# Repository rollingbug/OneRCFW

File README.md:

# OneRCFW
An Arduino/AVR based flight controller for RC fixed wing.  

    - 5 input channels (Throttle, Ailerons, Elevator, Rudder, flight mode)  
    - 4 output channels (0.5 us resolution PWM/PPM signal generator).  
    - Airplane NED attitude tracking function (with 6 DOF sensor, 200 Hz attitude update rate).
    - Airplane auto level (roll and pitch) control function.  
    - Airplane heading lock control function.  
    - Airplane flight mode control function (manual mode, auto level mode and GPS mode).  
    - Airplane GPS return to home function (unstabled, still need to do more test!)
    - RC output mixer function (for normal airplane, delta wing and V tail).  
    - 6 DOF sensor calibration function.  
    - Radio control stick position calibration function.    
    - Airplane failsafe function.  
    - Airplane configuration save/reload/reset function.  
    - Airplane runtime status monitoring function.  

  <br/><br/><br/>

Details:
---------------------
Flight controller source code: [OneRCFW](https://github.com/rollingbug/OneRCFW/tree/master/OneRCFW)  
Flight controller schematic and PCB layout: [OneRCSchematic_v1](https://github.com/rollingbug/OneRCFW/tree/master/OneRCSchematic/OneRCSchematic_v1)  
Flight controller test video: [20171029 FC test in very windy (12.5m/s) day.](https://www.youtube.com/watch?v=OjTpQ1Ft-OE)  
GUI monitoring tool: [OneRCGUI](https://github.com/rollingbug/OneRCFW/tree/master/OneRCGUI)  
Design documents: [OneRCDesignDoc](https://github.com/rollingbug/OneRCFW/tree/master/OneRCDesignDoc)   

Build and Installation:
---------------------
1. Prepare Arduino 1.6.9 IDE.
2. Click the **OneRCAirplane.ino** to launch Arduino IDE. 
3. Change board type setting to "Arduino Nano" or "Pro Mini" and correct UART port setting.
4. Build and upload the firmware to Arduino or customized PCB.
5. Connect the Radio receiver to flight controller.
6. Check the channel output signal and the status of on board LEDs.<br/><br/><br/>

For Simulation mode:
---------------------
1. Download and instll FlightGear, and copy the protocol and configuration file to speicfic folder.
    - Copy [MAVLink.xml](https://github.com/rollingbug/OneRCFW/tree/master/OneRCFlightGearConf/MAVLink.xml) to FlightGear\data\Protocol\
    - Copy [.fgfsrc](https://github.com/rollingbug/OneRCFW/tree/master/OneRCFlightGearConf/.fgfsrc) to C:\Documents and Settings\{User name}\
2. Modify the #define IMU_SENSOR_MPU6050 in imu_ctrl.h, change to #define IMU_SENSOR_FG_SIM.
3. Rebuild and upload the firmware to Arduino.
4. Modify the COM port setting in both the [MP_fdm_nmea.py](https://github.com/rollingbug/OneRCFW/tree/master/OneRCGUI/MP_fdm_nmea.py) and [MP_fdm_sim.py](https://github.com/rollingbug/OneRCFW/tree/master/OneRCGUI/MP_fdm_sim.py), and lanuch these 2 files.
5. Lanuch fgfs.exe and enjoy the flight in simulator.

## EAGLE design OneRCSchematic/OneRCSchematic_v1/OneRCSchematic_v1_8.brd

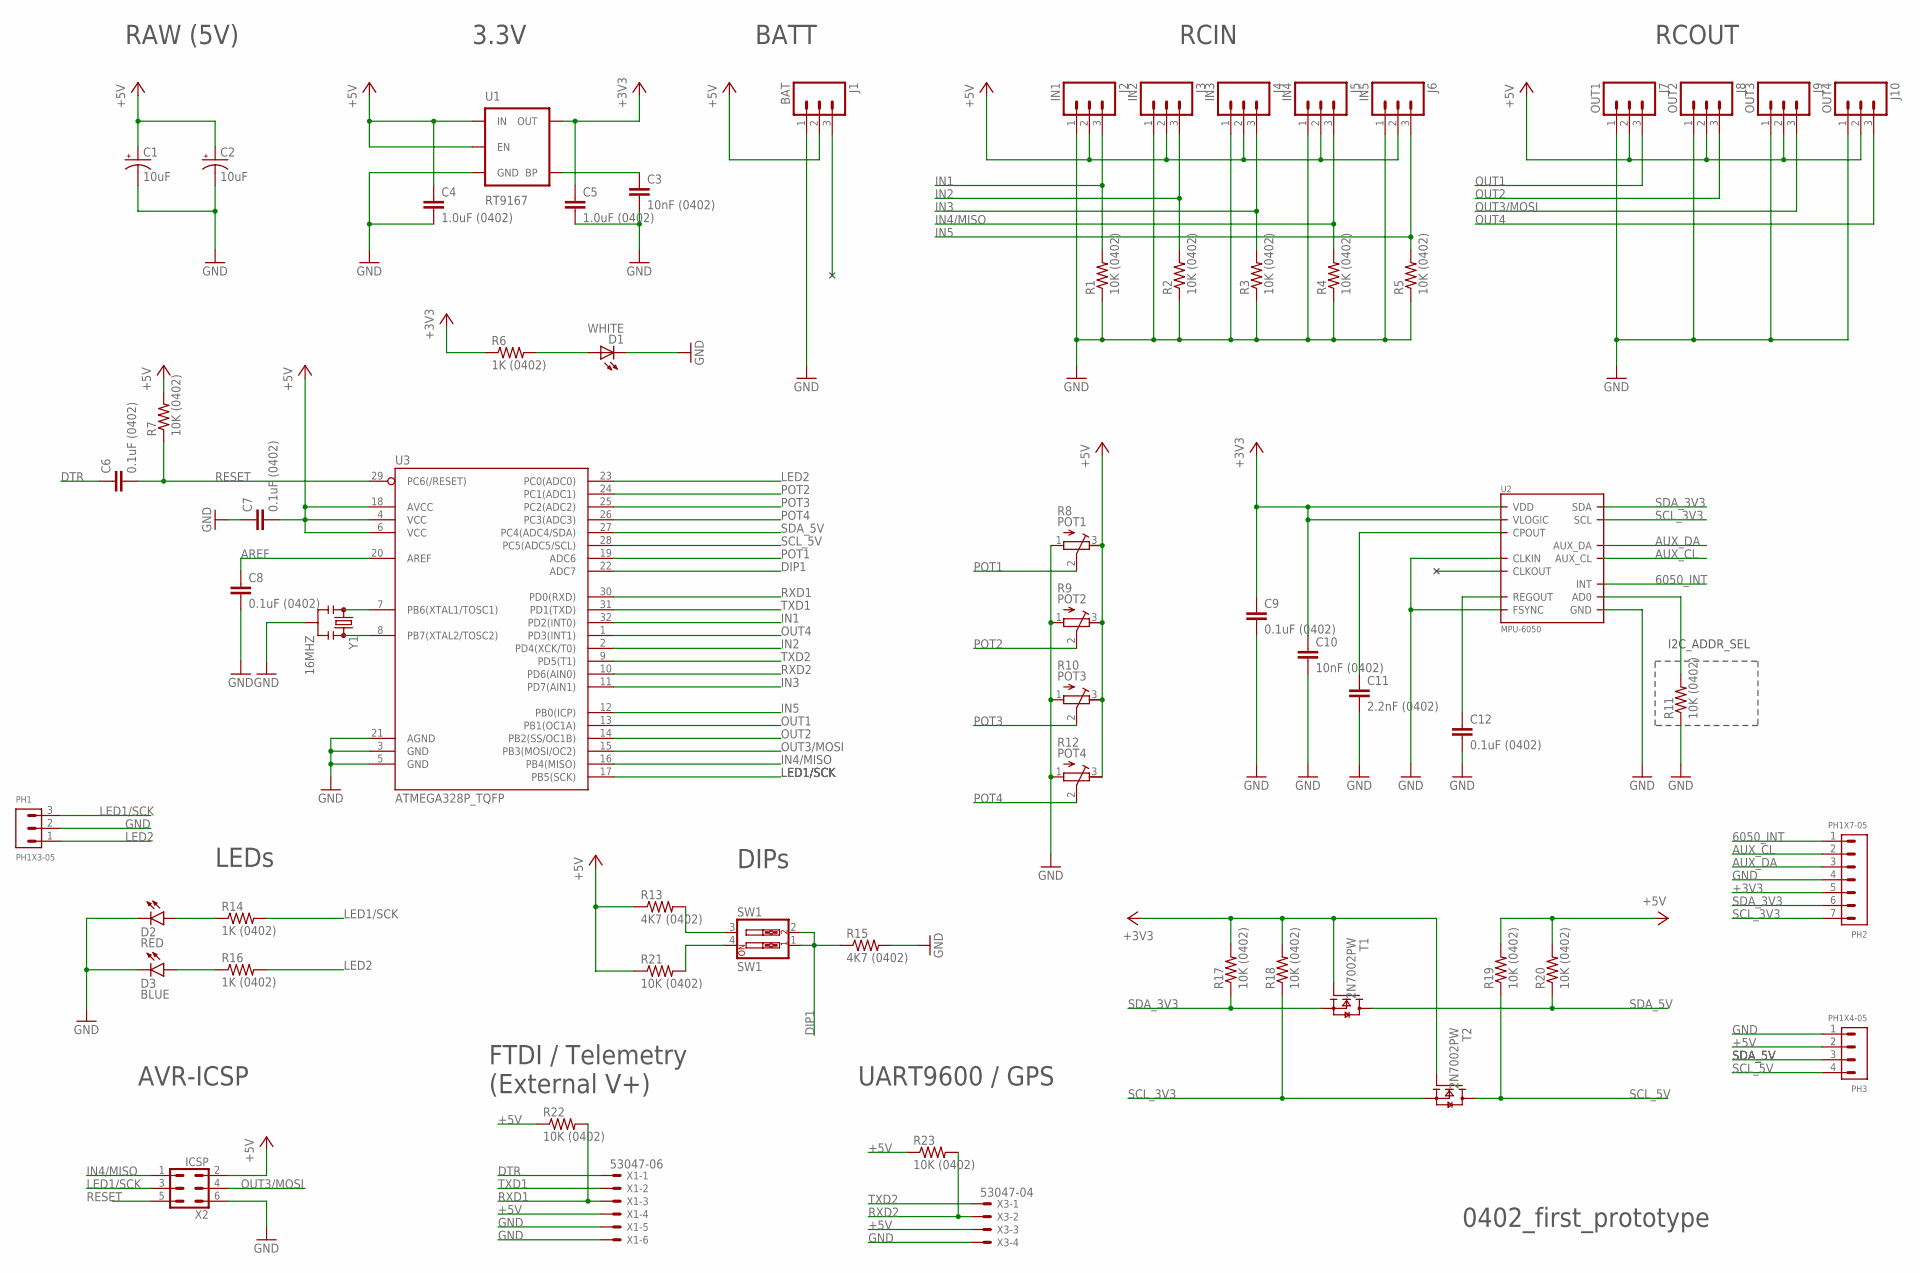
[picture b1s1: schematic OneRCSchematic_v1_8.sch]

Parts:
C1, C2: 10uF; EIA3216
C3, C10: 10nF (0402); 0402-CAP
C4, C5: 1.0uF (0402); 0402-CAP
C6, C7, C8, C9, C12: 0.1uF (0402); 0402-CAP
C11: 2.2nF (0402); 0402-CAP
D1: WHITE; 0402-LED
D2: RED; LED-0603
D3: BLUE; LED-0603
J1: BAT; 1X03
J2: IN1; 1X03
J3: IN2; 1X03
J4: IN3; 1X03
J5: IN4; 1X03
J6: IN5; 1X03
J7: OUT1; 1X03
J8: OUT2; 1X03
J9: OUT3; 1X03
J10: OUT4; 1X03
PH1: PH1X3-05; PH005-1-3
PH2: PH1X7-05; PH005-1-7
PH3: PH1X4-05; PH005-1-4
R1, R2, R3, R4, R5, R7, R11, R17, R18, R19, R20, R21, R22, R23: 10K (0402); 0402-RES
R6, R14, R16: 1K (0402); 0402-RES
R8: POT1; RTRIM3202
R9: POT2; RTRIM3202
R10: POT3; RTRIM3202
R12: POT4; RTRIM3202
R13, R15: 4K7 (0402); 0402-RES
SW1: SW1; DIPSWITCH-02-50MIL
T1, T2: 2N7002PW; SOT323
U1: RT9167; SOT23-5
U2: MPU-6050; QFN.24.4X4
U3: ATMEGA328P_TQFP; TQFP32-08
X1: 53047-06
X2: ICSP; PHB_1MM27_2X03_SNT
X3: 53047-04
Y1: 16MHZ; RESONATOR-SMD

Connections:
6050_INT: PH2.1, U2.12 (INT)
+3V3: C5.1, C9.1, C10.1, PH2.5, R6.1, R17.2, R18.2, T1.1 (G), T2.1 (G), U1.5 (OUT), U2.8 (VLOGIC), U2.13 (VDD)
+5V: C1.A (+), C2.A (+), C4.1, C7.2, J1.2, J2.2, J3.2, J4.2, J5.2, J6.2, J7.2, J8.2, J9.2, J10.2, PH3.2, R7.2, R8.3 (E), R9.3 (E), R10.3 (E), R12.3 (E), R13.1, R19.2, R20.2, R21.1, R22.1, R23.1, U1.1 (IN), U1.3 (EN), U3.4 (VCC), U3.6 (VCC), U3.18 (AVCC), X1.4, X2.2, X3.3
AREF: C8.1, U3.20 (AREF)
AUX_CL: PH2.2, U2.7 (AUX_CL)
AUX_DA: PH2.3, U2.6 (AUX_DA)
DIP1: R15.1, SW1.1, SW1.2, U3.22 (ADC7)
DTR: C6.1, X1.1
GND: C1.C (-), C2.C (-), C3.2, C4.2, C5.2, C7.1, C8.2, C9.2, C10.2, C11.2, C12.2, D1.C, D2.C, D3.C, J1.1, J2.1, J3.1, J4.1, J5.1, J6.1, J7.1, J8.1, J9.1, J10.1, PH1.2, PH2.4, PH3.1, R1.1, R2.1, R3.1, R4.1, R5.1, R8.1 (A), R9.1 (A), R10.1 (A), R11.1, R12.1 (A), R15.2, U1.2 (GND), U2.1 (CLKIN), U2.11 (FSYNC), U2.18 (GND), U3.3 (GND), U3.5 (GND), U3.21 (AGND), X1.5, X1.6, X2.6, X3.4, Y1.2
IN1: J2.3, R1.2, U3.32 (PD2(INT0))
IN2: J3.3, R2.2, U3.2 (PD4(XCK/T0))
IN3: J4.3, R3.2, U3.11 (PD7(AIN1))
IN4/MISO: J5.3, R4.2, U3.16 (PB4(MISO)), X2.1
IN5: J6.3, R5.2, U3.12 (PB0(ICP))
LED1/SCK: PH1.3, R14.2, U3.17 (PB5(SCK)), X2.3
LED2: PH1.1, R16.2, U3.23 (PC0(ADC0))
unnamed: D2.A, R14.1
unnamed: U3.7 (PB6(XTAL1/TOSC1)), Y1.1
unnamed: U3.8 (PB7(XTAL2/TOSC2)), Y1.3
unnamed: D3.A, R16.1
unnamed: D1.A, R6.2
unnamed: C3.1, U1.4 (BP)
unnamed: C11.1, U2.20 (CPOUT)
unnamed: C12.1, U2.10 (REGOUT)
unnamed: R13.2, SW1.3
unnamed: R21.2, SW1.4
unnamed: R11.2, U2.9 (AD0)
OUT1: J7.3, U3.13 (PB1(OC1A))
OUT2: J8.3, U3.14 (PB2(SS/OC1B))
OUT3/MOSI: J9.3, U3.15 (PB3(MOSI/OC2)), X2.4
OUT4: J10.3, U3.1 (PD3(INT1))
POT1: R8.2 (S), U3.19 (ADC6)
POT2: R9.2 (S), U3.24 (PC1(ADC1))
POT3: R10.2 (S), U3.25 (PC2(ADC2))
POT4: R12.2 (S), U3.26 (PC3(ADC3))
RESET: C6.2, R7.1, U3.29 (PC6(/RESET)), X2.5
RXD1: R22.2, U3.30 (PD0(RXD)), X1.3
RXD2: R23.2, U3.10 (PD6(AIN0)), X3.2
SCL_3V3: PH2.7, R18.1, T2.2 (S), U2.23 (SCL)
SCL_5V: PH3.4, R19.1, T2.3 (D), U3.28 (PC5(ADC5/SCL))
SDA_3V3: PH2.6, R17.1, T1.2 (S), U2.24 (SDA)
SDA_5V: PH3.3, R20.1, T1.3 (D), U3.27 (PC4(ADC4/SDA))
TXD1: U3.31 (PD1(TXD)), X1.2
TXD2: U3.9 (PD5(T1)), X3.1

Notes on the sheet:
LEDs
RCIN
RCOUT
3.3V
RAW (5V)
AVR-ICSP
FTDI / Telemetry (External V+)
UART9600 / GPS
DIPs
0402_first_prototype
I2C_ADDR_SEL
BATT

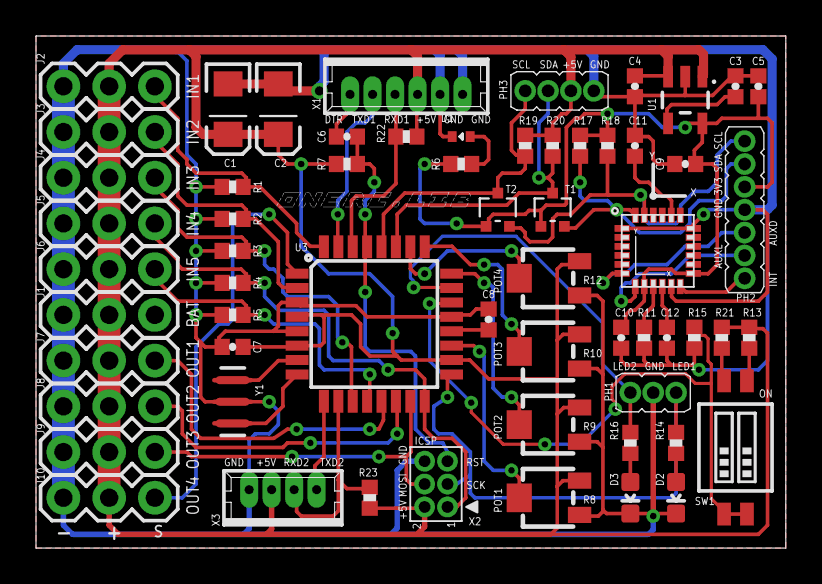
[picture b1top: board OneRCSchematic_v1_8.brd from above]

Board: 2 copper layers, 41.7 x 28.4 mm, 62 parts (0 on the bottom side), 44 nets.

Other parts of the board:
U$2: ONE_RX_LOG_TINY_TOP

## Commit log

2017-12-17 [OneRCFW]
    1. Import v0.1.0.
    - Auto level function.
    - Maintaining heading angle based on gyroscope.
    - FC configuration save/clean/load functions.
    - Return to home according to GPS navigation information (unstable, need to do more test).
    - RCIN calibration functions:
2018-01-21 [OneRCFW]
    1. Add design documents and update README.md.
2018-01-21 [OneRCFW]
    1. Picture link test.
2018-01-21 [OneRCFW]
    1. Rearranged README.md.
2018-01-21 [OneRCFW]
    1. Sorry, just correct the picture link.
2018-09-01 [OneRCFW]
    1. Committed latest modification:
    - Modified MPU6050 FIFO sampling rate to 1000 Hz by default.
    - Modified Airplane_FlyCtrl function, increase the pitch setpoint (angle of attack) when the FC performing bank turn for "returning to home".
    * I did the field trial, but the airplane still lost altitude quickly while it performing the bank turn (return to home mode).
    * Although I already limit the maximum bank turn angle to +-30 degree in code, but the airplane still rolls more than 30 degree while it performing the bank turn (return to home mode).
    - Most of functions in this firmware are quite stable EXCEPT the return to home function.
2018-09-01 1. Update README.md.
2018-09-01 Correct README.md
2019-06-02 Update README.md
    Correct board type setting description.

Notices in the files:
parts and their libraries:
SparkFun-Capacitors: Licensing: Creative Commons ShareAlike 4.0 International - https://creativecommons.org/licenses/by-sa/4.0
